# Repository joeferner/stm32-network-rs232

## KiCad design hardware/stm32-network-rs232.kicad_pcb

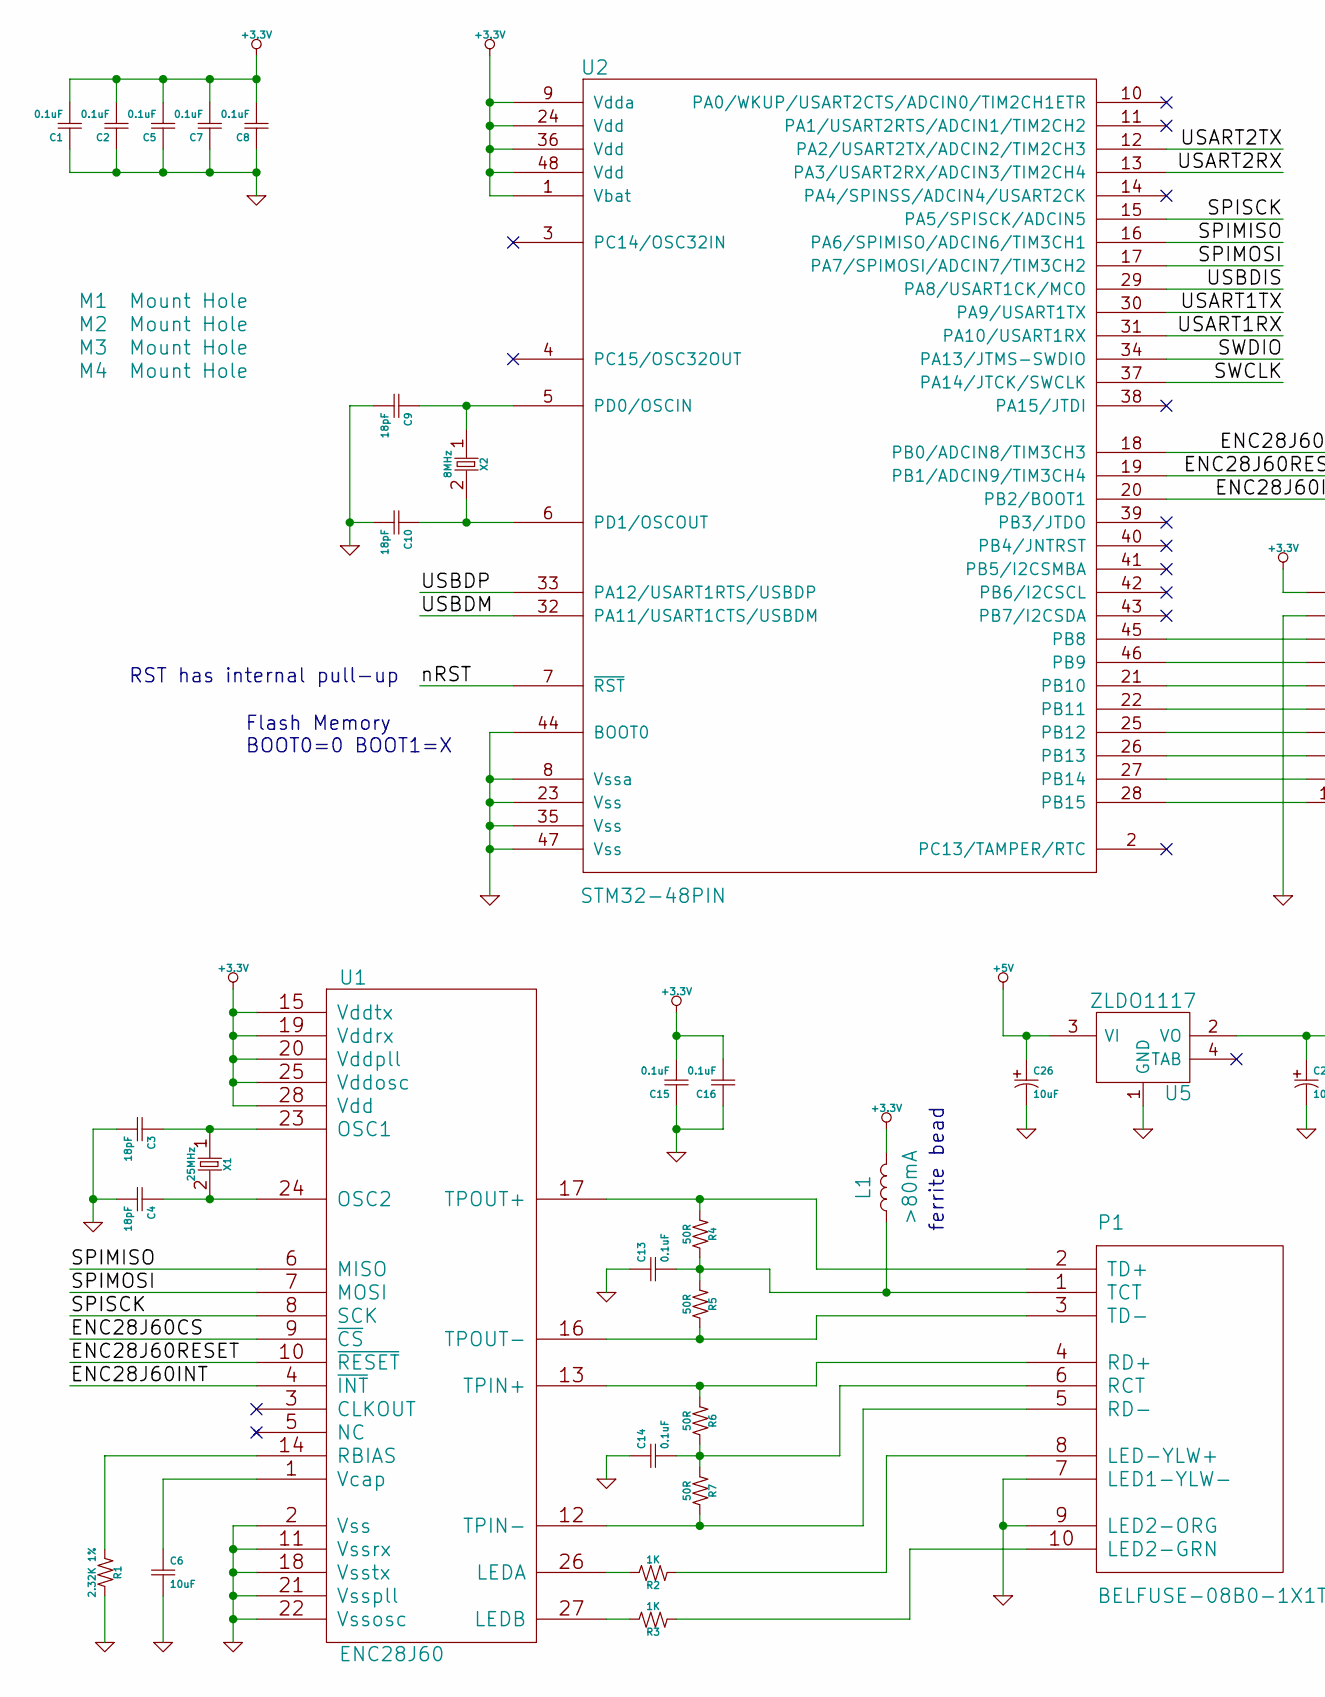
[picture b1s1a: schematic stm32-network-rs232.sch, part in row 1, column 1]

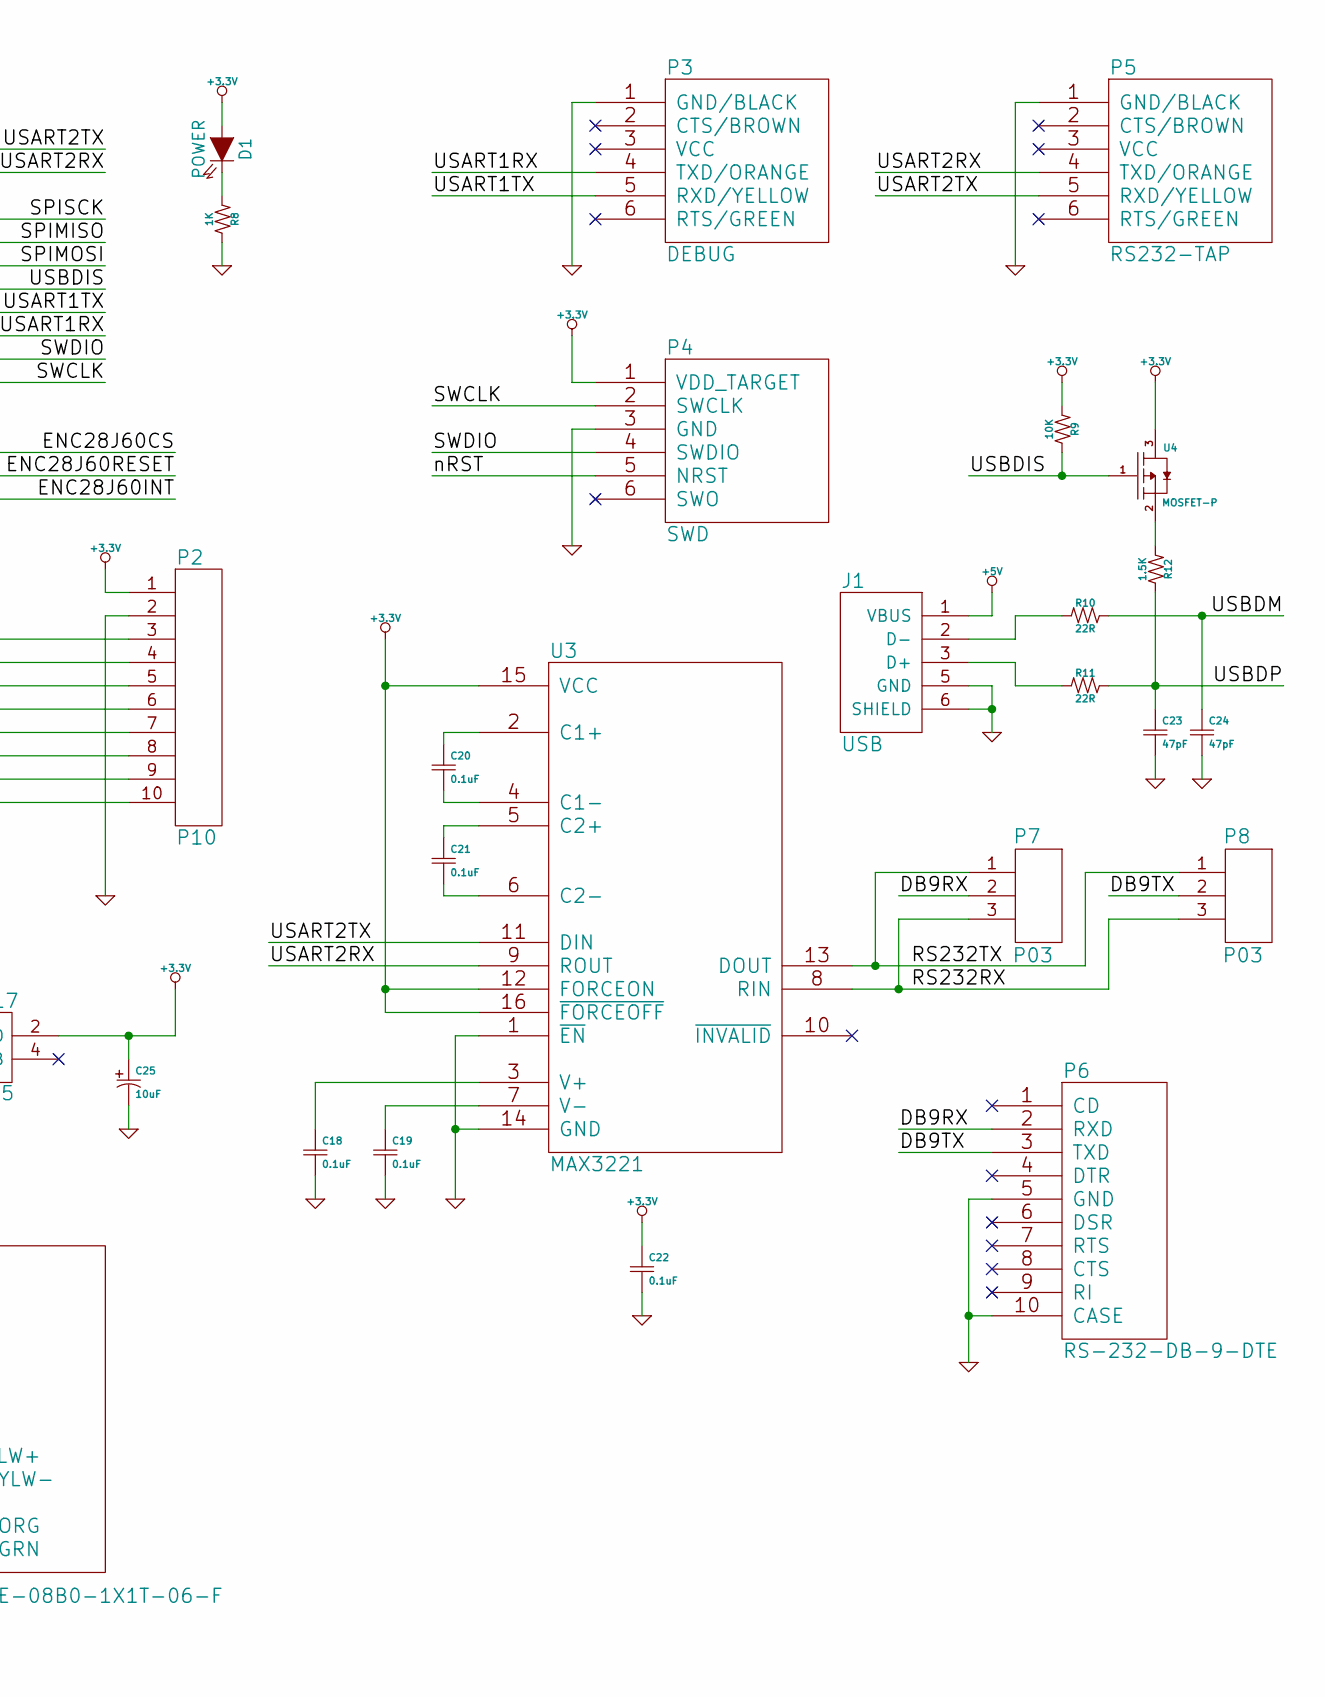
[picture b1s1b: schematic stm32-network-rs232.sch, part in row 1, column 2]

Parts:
C1, C2, C5, C7, C8, C13, C14, C15, C16, C18, C19, C20, C21, C22: 0.1uF; CAPC2012X100N
C3, C4, C9, C10: 18pF; CAPC2012X100N
C6: 10uF; CAPC2012X100N
C23, C24: 47pF; CAPC2012X100N
C25, C26: 10uF; CAPCP2012X100N
D1: POWER; LEDC3216X100N; MfgPartNumber LTST-C150GKT
J1: USB; JST_UB-MC5BR3-SD204-4S-NMP; MfgPartNumber UB-MC5BR3-SD204-4S-TB NMP
L1: >80mA; RESC2012X100N; MfgPartNumber HZ0805E601R-10
M1, M2, M3, M4: Mount Hole; MTGNP565H328Z565P
P1: BELFUSE-08B0-1X1T-06-F; BEL-FUSE-08B0-1X1T-06-F; MfgPartNumber 08B0-1X1T-06-F
P2: P10; HDRV10W66P254_1X10_1006X249X838P
P3: DEBUG; HDRV6W66P254_1X6_1524X249X838P
P4: SWD; HDRV6W66P254_1X6_1524X249X838P
P5: RS232-TAP; HDRV6W66P254_1X6_1524X249X838P
P6: RS-232-DB-9-DTE; TECONN-5747840-2; MfgPartNumber 5747840-2
P7, P8: P03; HDRV3W66P254_1X3_762X249X838P
R1: 2.32K 1%; RESC2012X100N; MfgPartNumber RNCP0805FTD2K32
R2, R3, R8: 1K; RESC2012X100N; MfgPartNumber RC0805JR-071KL
R4, R5, R6, R7: 50R; RESC2012X100N; MfgPartNumber RNCP0805FTD49R9
R9: 10K; RESC2012X100N; MfgPartNumber ESR10EZPJ103
R10, R11: 22R; RESC2012X100N; MfgPartNumber RNCP0805FTD22R1
R12: 1.5K; RESC2012X100N; MfgPartNumber ESR10EZPJ152
U1: ENC28J60; SOP65P780X200-28N; MfgPartNumber ENC28J60/SS
U2: STM32-48PIN; QFP50P900X900X160-48N; MfgPartNumber STM32F103CBT6
U3: MAX3221; SOP65P640X120-16N; MfgPartNumber MAX3221CPWR
U4: MOSFET-P; SOT95P237X112_123-3N; MfgPartNumber ZXMP2120FFTA
U5: ZLDO1117; SOT230P700X180-4N; MfgPartNumber ZLDO1117G33TA
X1: 25MHz; XTAL8045X200N; MfgPartNumber NX8045GB-25.000000MHZ
X2: 8MHz; XTAL8045X200N; MfgPartNumber NX8045GB-8.000000MHZ

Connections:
+3.3V: C1.2, C2.2, C5.2, C7.2, C8.2, C15.2, C16.2, C22.1, C25.1, D1.1 (A), L1.1, P2.1, P4.1 (VDD_TARGET), R9.2, U1.15 (Vddtx), U1.19 (Vddrx), U1.20 (Vddpll), U1.25 (Vddosc), U1.28 (Vdd), U2.1 (Vbat), U2.9 (Vdda), U2.24 (Vdd), U2.36 (Vdd), U2.48 (Vdd), U3.12 (FORCEON), U3.15 (VCC), U3.16 (~FORCEOFF), U4.3, U5.2 (VO)
+5V: C26.1, J1.1 (VBUS), U5.3 (VI)
/DB9RX: P6.2 (RXD), P7.2
/DB9TX: P6.3 (TXD), P8.2
/ENC28J60CS: U1.9 (~CS), U2.18 (PB0/ADCIN8/TIM3CH3)
/ENC28J60INT: U1.4 (~INT), U2.20 (PB2/BOOT1)
/ENC28J60RESET: U1.10 (~RESET), U2.19 (PB1/ADCIN9/TIM3CH4)
/RS232RX: P7.3, P8.3, U3.8 (RIN)
/RS232TX: P7.1, P8.1, U3.13 (DOUT)
/SPIMISO: U1.6 (MISO), U2.16 (PA6/SPIMISO/ADCIN6/TIM3CH1)
/SPIMOSI: U1.7 (MOSI), U2.17 (PA7/SPIMOSI/ADCIN7/TIM3CH2)
/SPISCK: U1.8 (SCK), U2.15 (PA5/SPISCK/ADCIN5)
/SWCLK: P4.2 (SWCLK), U2.37 (PA14/JTCK/SWCLK)
/SWDIO: P4.4 (SWDIO), U2.34 (PA13/JTMS-SWDIO)
/USART1RX: P3.4 (TXD/ORANGE), U2.31 (PA10/USART1RX)
/USART1TX: P3.5 (RXD/YELLOW), U2.30 (PA9/USART1TX)
/USART2RX: P5.4 (TXD/ORANGE), U2.13 (PA3/USART2RX/ADCIN3/TIM2CH4), U3.9 (ROUT)
/USART2TX: P5.5 (RXD/YELLOW), U2.12 (PA2/USART2TX/ADCIN2/TIM2CH3), U3.11 (DIN)
/USBDIS: R9.1, U2.29 (PA8/USART1CK/MCO), U4.1
/USBDM: C24.1, R10.1, U2.32 (PA11/USART1CTS/USBDM)
/USBDP: C23.1, R11.1, R12.1, U2.33 (PA12/USART1RTS/USBDP)
/nRST: P4.5 (NRST), U2.7 (~RST)
GNDPWR: C1.1, C2.1, C3.2, C4.2, C5.1, C6.2, C7.1, C8.1, C9.2, C10.2, C13.1, C14.1, C15.1, C16.1, C18.2, C19.2, C22.2, C23.2, C24.2, C25.2, C26.2, J1.5 (GND), J1.6 (SHIELD), P1.7 (LED1-YLW-), P1.9 (LED2-ORG), P2.2, P3.1 (GND/BLACK), P4.3 (GND), P5.1 (GND/BLACK), P6.5 (GND), P6.10 (CASE), R1.1, R8.1, U1.2 (Vss), U1.11 (Vssrx), U1.18 (Vsstx), U1.21 (Vsspll), U1.22 (Vssosc), U2.8 (Vssa), U2.23 (Vss), U2.35 (Vss), U2.44 (BOOT0), U2.47 (Vss), U3.1 (~EN), U3.14 (GND), U5.1 (GND)
unnamed: C3.1, U1.23 (OSC1), X1.1
unnamed: C4.1, U1.24 (OSC2), X1.2
unnamed: C6.1, U1.1 (Vcap)
unnamed: C9.1, U2.5 (PD0/OSCIN), X2.1
unnamed: C10.1, U2.6 (PD1/OSCOUT), X2.2
unnamed: C13.2, L1.2, P1.1 (TCT), R4.1, R5.2
unnamed: C14.2, P1.6 (RCT), R6.1, R7.2
unnamed: C18.1, U3.3 (V+)
unnamed: C19.1, U3.7 (V-)
unnamed: C20.1, U3.2 (C1+)
unnamed: C20.2, U3.4 (C1-)
unnamed: C21.1, U3.5 (C2+)
unnamed: C21.2, U3.6 (C2-)
unnamed: D1.2 (K), R8.2
unnamed: J1.2 (D-), R10.2
unnamed: J1.3 (D+), R11.2
unnamed: P1.2 (TD+), R4.2, U1.17 (TPOUT+)
unnamed: P1.3 (TD-), R5.1, U1.16 (TPOUT-)
unnamed: P1.4 (RD+), R6.2, U1.13 (TPIN+)
unnamed: P1.5 (RD-), R7.1, U1.12 (TPIN-)
unnamed: P1.8 (LED-YLW+), R2.2
unnamed: P1.10 (LED2-GRN), R3.2
unnamed: P2.3, U2.45 (PB8)
unnamed: P2.4, U2.46 (PB9)
unnamed: P2.5, U2.21 (PB10)
unnamed: P2.6, U2.22 (PB11)
unnamed: P2.7, U2.25 (PB12)
unnamed: P2.8, U2.26 (PB13)
unnamed: P2.9, U2.27 (PB14)
unnamed: P2.10, U2.28 (PB15)
unnamed: R1.2, U1.14 (RBIAS)
unnamed: R2.1, U1.26 (LEDA)
unnamed: R3.1, U1.27 (LEDB)
unnamed: R12.2, U4.2

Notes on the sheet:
Flash Memory BOOT0=0 BOOT1=X
RST has internal pull-up
ferrite bead

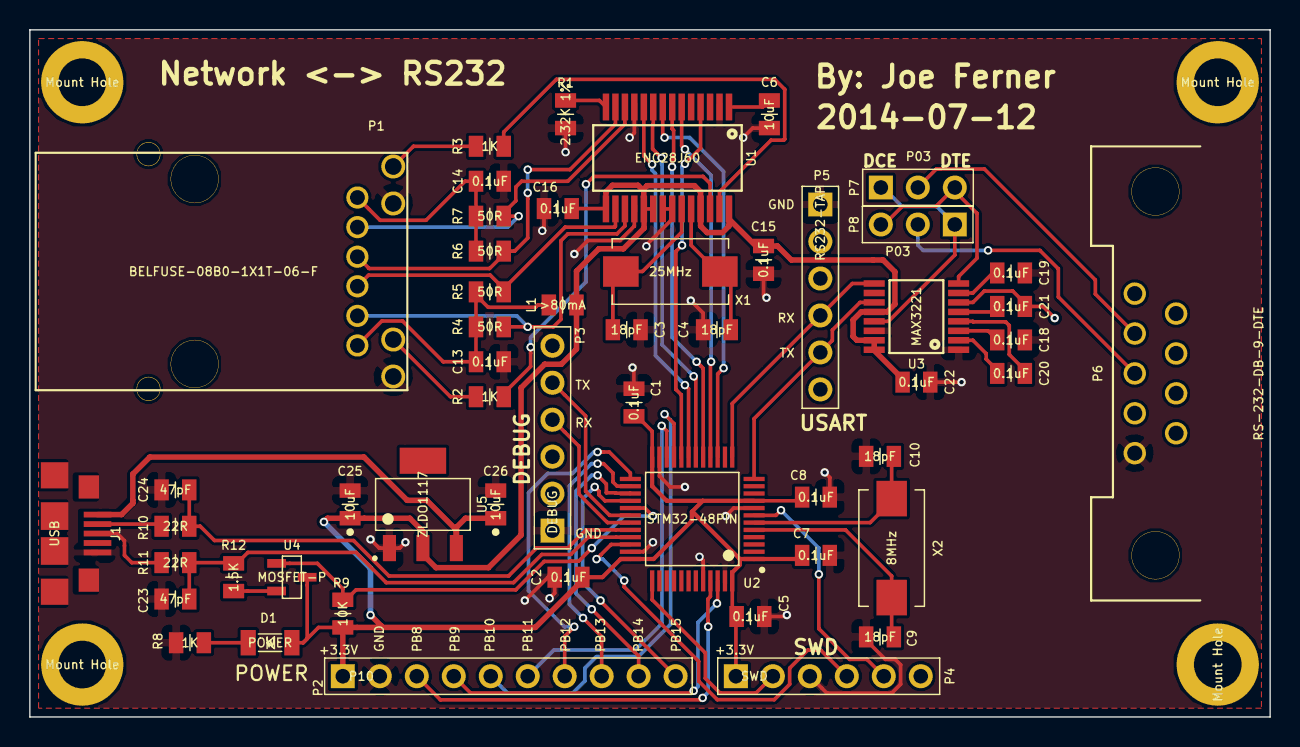
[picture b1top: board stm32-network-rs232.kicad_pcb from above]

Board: 2 copper layers, 85.2 x 47.2 mm, 57 parts (0 on the bottom side), 57 nets.

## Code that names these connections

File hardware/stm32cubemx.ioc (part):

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Mcu.Name=STM32F103C(8-B)Tx
Mcu.Package=LQFP48
Mcu.UserName=STM32F103CBTx
PA10.GPIOParameters=GPIO_Label
PA10.GPIO_Label=DEBUG_USART_RX
PA10.Mode=Asynchronous
PA10.Signal=USART1_RX
PA11.Mode=Dummy
PA11.Signal=USB_DM
PA12.Mode=Dummy
PA12.Signal=USB_DP
PA13.Mode=Serial-Wire
PA13.Signal=SYS_JTMS-SWDIO
PA14.Mode=Serial-Wire
PA14.Signal=SYS_JTCK-SWCLK
PA2.GPIOParameters=GPIO_Label
PA2.GPIO_Label=RS232_TX
PA2.Mode=Asynchronous
PA2.Signal=USART2_TX
PA3.GPIOParameters=GPIO_Label
PA3.GPIO_Label=RS232_RX
PA3.Mode=Asynchronous
PA3.Signal=USART2_RX
PA5.Mode=Full-Duplex-Master
PA5.Signal=SPI1_SCK
PA6.Mode=Full-Duplex-Master
PA6.Signal=SPI1_MISO
PA7.Mode=Full-Duplex-Master
PA7.Signal=SPI1_MOSI
PA8.GPIOParameters=GPIO_Label
PA8.GPIO_Label=USB_DISCONNECT
PA8.Signal=GPIO_Output
PA9.GPIOParameters=GPIO_Label
PA9.GPIO_Label=DEBUG_USART_TX
PA9.Mode=Asynchronous
PA9.Signal=USART1_TX
PB0.GPIOParameters=GPIO_Label
PB0.GPIO_Label=ENC28J60_CS
PB0.Signal=GPIO_Output
PB1.GPIOParameters=GPIO_Label
PB1.GPIO_Label=ENC28J60_RESET
PB1.Signal=GPIO_Output
PB10.GPIOParameters=GPIO_Label
PB10.GPIO_Label=AUX2
PB10.Signal=GPIO_Output
PB11.GPIOParameters=GPIO_Label
PB11.GPIO_Label=AUX3
PB11.Signal=GPIO_Output
PB12.GPIOParameters=GPIO_Label
PB12.GPIO_Label=AUX4
PB12.Signal=GPIO_Output
PB13.GPIOParameters=GPIO_Label
PB13.GPIO_Label=AUX5
PB13.Signal=GPIO_Output
PB14.GPIOParameters=GPIO_Label
PB14.GPIO_Label=AUX6
PB14.Signal=GPIO_Output
PB15.GPIOParameters=GPIO_Label
PB15.GPIO_Label=AUX7
PB15.Signal=GPIO_Output
PB2.GPIOParameters=GPIO_Label
PB2.GPIO_Label=ENC28J60_INT
PB2.Signal=GPIO_Input
PB8.GPIOParameters=GPIO_Label
PB8.GPIO_Label=AUX0
PB8.Signal=GPIO_Output
PB9.GPIOParameters=GPIO_Label
PB9.GPIO_Label=AUX1
PB9.Signal=GPIO_Output
PD0-OSC_IN.Mode=HSE-External-Oscillator
PD0-OSC_IN.Signal=SYS_OSC_IN
PD1-OSC_OUT.Mode=HSE-External-Oscillator
PD1-OSC_OUT.Signal=SYS_OSC_OUT

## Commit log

2014-06-24 initial
2014-06-24 save/update kicad library
2014-06-24 initial firmware
2014-06-24 add codeblocks project file
2014-06-24 blink led
2014-06-24 initial uip
2014-06-25 project
2014-06-25 working stlink
2014-06-25 progress
2014-06-25 less errors
2014-06-27 builds
2014-07-01 comms working
2014-07-01 working
2014-07-01 faster
2014-07-03 stm32cubemx
2014-07-04 update libs
2014-07-05 max3221
2014-07-05 fix pins
2014-07-05 BELFUSE-08B0-1X1T-06-F
2014-07-05 remove unused parts
2014-07-05 schematic complete
2014-07-06 add 3.3V reg
2014-07-06 more mods
2014-07-07 add rx/tx toggles
2014-07-08 more modules
2014-07-08 filters
2014-07-09 initial layout
2014-07-09 update kicadlib
2014-07-09 update from kicadlib
2014-07-09 upgrade to new modules part 1
2014-07-09 finish upgrade of mods
2014-07-12 board routing
2014-07-12 board layout complete
2014-07-12 increase power trace widths
2014-07-12 more board changes
2014-07-19 update footprints
2014-07-19 update kicad lib
2014-07-19 v2014-07-12
2014-07-19 line up labels
2014-08-01 add manufacturer part numbers
2014-08-03 move usb port in a little
2014-08-03 working usart2
2014-08-04 simple server
2014-08-05 initial work of converting usart rx to dma
2014-08-05 refactor rs232 usart to use dma
2014-08-05 refactor rs232_write to by async and handle writing in rs232_tick
2014-08-06 usart dma working
2014-08-06 contiki upgrade (closes issue #5)
2014-08-07 compiling
2014-08-08 sending initial dhcp
2014-08-08 working dhcp
2014-08-08 telnet process starting to work
2014-08-09 copy data from rs232 to network and back agiain
2014-08-09 nudge usb connector to make more room
2014-08-12 working mdns
2014-09-05 remove kicad-library subtree
2014-09-07 add ignore
2015-03-28 update gitignore
2015-03-29 change mac address
2015-04-07 fix pin order on DB-9
2015-04-07 update from kicad-library
2015-04-10 initial move to stm32lib
2015-04-10 working network
2015-04-11 initial httpd work
2015-04-12 remove firmware dir
2015-04-12 move firmware-stm32lib to firmware
2015-04-12 working iwdg
2015-04-12 add timeout to http
2015-04-13 switch to irq
2015-04-14 use interrupts
2015-04-15 fix new line characters
2015-04-15 don't clear the RXNE flag, this will clear on read
2015-04-20 network debug
2015-04-21 move debug_networkSetup to after dhcp
2015-04-21 use git submodules for stm32lib and contiki
2015-04-25 change ip address of debug
2015-05-14 reset after 5 hours
2015-05-14 remove reset logic since this doesn't fix the problem
2015-05-31 use standard toolchain
2015-06-13 update contiki
2015-06-14 switched over to using UDP
2015-09-18 update contiki and stm32lib
2015-11-05 use contiki's ENC28J60 support
2015-11-06 new firmware start
2015-11-06 removed utils, added contiki
2015-11-06 change utils to submodule
2015-11-06 move syscalls to utils
2015-11-07 working debug
2015-11-07 dma ring buffer
2015-11-08 moved debug into utils
2015-11-08 working rs232
2015-11-09 more networking
2015-11-09 add watchdog support
2015-11-09 remove old firmware
2015-11-09 moved firmware-new to firmware
2015-11-10 turn off contiki log
2016-12-07 updated Makefile
2017-02-26 rewrite firmware to custom firmware
